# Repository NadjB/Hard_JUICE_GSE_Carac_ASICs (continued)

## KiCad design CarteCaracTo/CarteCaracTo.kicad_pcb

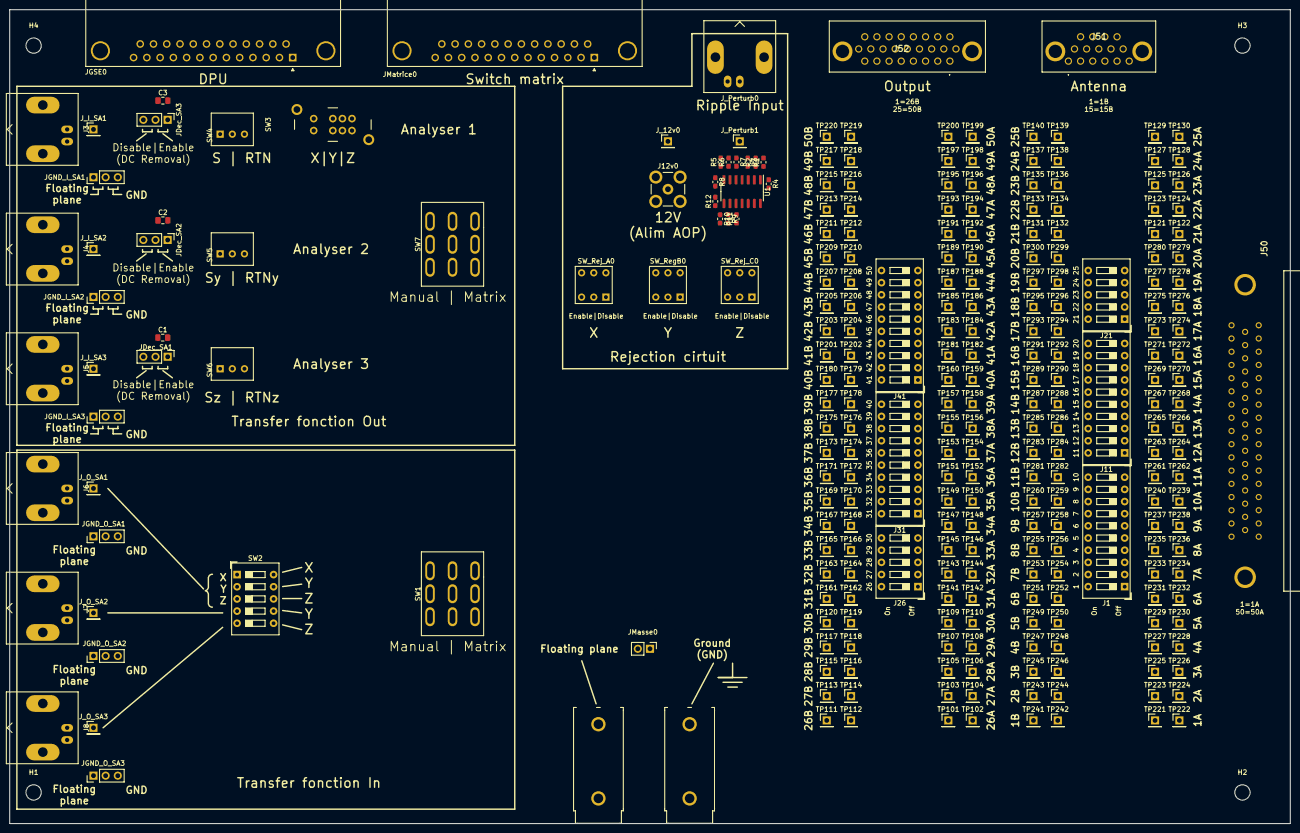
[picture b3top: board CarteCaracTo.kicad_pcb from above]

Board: 6 copper layers, 267.5 x 170.0 mm, 269 parts (0 on the bottom side), 129 nets, no tracks yet.

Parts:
C1, C2, C3: C; C_0805_2012Metric_Pad1.15x1.40mm_HandSolder
H1, H2, H3, H4: MountingHole; MountingHole_3.2mm_M3
J1, J11, J31, J41: Conn_02x10_Counter_Clockwise; SW_DIP_SPSTx10_Slide_9.78x27.58mm_W7.62mm_P2.54mm
J3, J4, J5, J6, J7, J8: Conn_Coaxial; BNC_Amphenol_B6252HB-NPP3G-50_Horizontal
J12v0: Conn_Coaxial; SMB_Jack_Vertical
J21, J26: Conn_02x05_Counter_Clockwise; SW_DIP_SPSTx05_Slide_9.78x14.88mm_W7.62mm_P2.54mm
J50: Sub-D50_F; DD50S564TLF
J51: DB15_Male_MountingHoles; DCCM15PCBRPN
J52: DB25_Female_MountingHoles; DCCM25SCBRPN
JDec_SA1, JDec_SA2, JDec_SA3: Conn_01x03; PinHeader_1x03_P2.54mm_Vertical
JGND_I_SA1, JGND_I_SA2, JGND_I_SA3: Conn_01x03; PinHeader_1x03_P2.54mm_Vertical
JGND_O_SA1, JGND_O_SA2, JGND_O_SA3: Conn_01x03; PinHeader_1x03_P2.54mm_Vertical
JGSE0: DB25_Male_MountingHoles; DSUB-25_Male_Horizontal_P2.77x2.84mm_EdgePinOffset9.90mm_Ho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
JMasse0: Conn_01x02; PinHeader_1x02_P2.54mm_Vertical
JMatrice0: DB25_Male_MountingHoles; DSUB-25_Male_Horizontal_P2.77x2.84mm_EdgePinOffset9.90mm_Ho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
J_12v0: Conn_01x01; PinHeader_1x01_P2.54mm_Vertical
J_I_SA1, J_I_SA2, J_I_SA3: Conn_01x01; PinHeader_1x01_P2.54mm_Vertical
J_O_SA1, J_O_SA2, J_O_SA3: Conn_01x01; PinHeader_1x01_P2.54mm_Vertical
J_Perturb0: Conn_Coaxial; BNC_Amphenol_B6252HB-NPP3G-50_Horizontal
J_Perturb1: Conn_01x01; PinHeader_1x01_P2.54mm_Vertical
R1, R2, R3, R4, R5, R6, R7, R8, R9, R10, R11, R12: R; R_0603_1608Metric_Pad1.05x0.95mm_HandSolder
SW1, SW7: SW_3PDT; SW_3PDT_M2032TNW01_NKK
SW2: SW_DIP_x05; SW_DIP_SPSTx05_Slide_9.78x14.88mm_W7.62mm_P2.54mm
SW3: SW_Slide_DP3T; Switch_DP3T_Slide_MHS233K
SW4, SW5, SW6: SW_SPDT; SW_SPDT_B12AP_NKK
SW_RegB0: SW_Push_DPDT; SW_DPDT_B22AP_NKK
SW_Rej_A0: SW_Push_DPDT; SW_DPDT_B22AP_NKK
SW_Rej_C0: SW_Push_DPDT; SW_DPDT_B22AP_NKK
TP101, TP102, TP103, TP104, TP105, TP106, TP107, TP108, TP109, TP110, TP111, TP112, TP113, TP114, TP115, TP116, TP117, TP118, TP119, TP120, TP121, TP122, TP123, TP124, TP125, TP126, TP127, TP128, TP129, TP130, TP131, TP132, TP133, TP134, TP135, TP136, TP137, TP138, TP139, TP140, TP141, TP142, TP143, TP144, TP145, TP146, TP147, TP148, TP149, TP150, TP151, TP152, TP153, TP154, TP155, TP156, TP157, TP158, TP159, TP160, TP161, TP162, TP163, TP164, TP165, TP166, TP167, TP168, TP169, TP170, TP171, TP172, TP173, TP174, TP175, TP176, TP177, TP178, TP179, TP180, TP181, TP182, TP183, TP184, TP185, TP186, TP187, TP188, TP189, TP190, TP191, TP192, TP193, TP194, TP195, TP196, TP197, TP198, TP199, TP200, TP201, TP202, TP203, TP204, TP205, TP206, TP207, TP208, TP209, TP210, TP211, TP212, TP213, TP214, TP215, TP216, TP217, TP218, TP219, TP220, TP221, TP222, TP223, TP224, TP225, TP226, TP227, TP228, TP229, TP230, TP231, TP232, TP233, TP234, TP235, TP236, TP237, TP238, TP239, TP240, TP241, TP242, TP243, TP244, TP245, TP246, TP247, TP248, TP249, TP250, TP251, TP252, TP253, TP254, TP255, TP256, TP257, TP258, TP259, TP260, TP261, TP262, TP263, TP264, TP265, TP266, TP267, TP268, TP269, TP270, TP271, TP272, TP273, TP274, TP275, TP276, TP277, TP278, TP279, TP280, TP281, TP282, TP283, TP284, TP285, TP286, TP287, TP288, TP289, TP290, TP291, TP292, TP293, TP294, TP295, TP296, TP297, TP298, TP299, TP300: TestPoint; PinHeader_1x01_P2.54mm_Vertical
TPGND0: TestPoint; Banana_test_point_4mm
TPV0: TestPoint; Banana_test_point_4mm
U1: OPA4376; SOIC-14_3.9x8.7mm_P1.27mm

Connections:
/1: J1.1, J50.1, JMatrice0.1, SW2.10, TP221.1, TP222.1
/01-10/1b-10b/sheet61AD0B7F/TPs: TP257.1, TP258.1
/01-10/sheet61ADBB5A/sheet61AD0B7F/TPs: TP237.1, TP238.1
/2: J1.2, J50.2, TP223.1, TP224.1
/3: J1.3, J50.3, JMatrice0.3, SW2.7, SW2.9, TP225.1, TP226.1
/4: J1.4, J50.4, TP227.1, TP228.1
/5: J1.5, J50.5, JMatrice0.5, SW2.6, SW2.8, TP229.1, TP230.1
/6: J1.6, J50.6, TP231.1, TP232.1
/9: J1.9, J50.9, JGSE0.3
/11: J11.1, J50.11, JGSE0.6, TP261.1, TP262.1
/11-20/1b-10b/sheet61AD0B7F/TPs: TP297.1, TP298.1
/11-20/sheet61ADBB5A/sheet61AD0B7F/TPs: TP277.1, TP278.1
/13: J11.3, J50.13, JGSE0.9, TP265.1, TP266.1
/16: J11.6, J50.16, TP271.1, TP272.1
/17: J11.7, J50.17, TP273.1, TP274.1
/18: J11.8, J50.18, TP275.1, TP276.1
/19: J11.9, J50.19, JGSE0.10
/20: J11.10, J50.20, JGSE0.11, TP279.1, TP280.1
/21: J21.1, J50.21, JGSE0.12, TP121.1, TP122.1
/22: J21.2, J50.22, JGSE0.14, TP123.1, TP124.1
/23: J21.3, J50.23, JGSE0.15, TP125.1, TP126.1
/24: J21.4, J50.24, JGSE0.16, TP127.1, TP128.1
/25: J21.5, J50.25, TP129.1, TP130.1
/26: J26.1, J50.26, JGSE0.2, JMatrice0.8, SW3.5, TP101.1, TP102.1
/27: J26.2, J50.27, JGSE0.1, JMatrice0.2, SW3.1, TP103.1, TP104.1
/29: J26.4, J50.29, JGSE0.7, JMatrice0.6, SW3.4, SW6.1, TP107.1, TP108.1
/30: J26.5, J50.30, JGSE0.8, JMatrice0.12, SW3.8, SW6.3, TP109.1, TP110.1
/31: J1.8, J31.1, J50.8, J50.31, TP141.1, TP142.1, TP235.1, TP236.1
/31-40/1b-10b/sheet61AD0B7F/TPs: TP177.1, TP178.1
/31-40/sheet61ADBB5A/sheet61AD0B7F/TPs: TP157.1, TP158.1
/32: J31.2, J50.32, TP143.1, TP144.1
/37: J31.7, J50.37, TP153.1, TP154.1
/40: J31.10, J50.40, JGSE0.4, JMatrice0.4, SW3.3, SW5.1, TP159.1, TP160.1
/41: J41.1, J50.41, JGSE0.5, JMatrice0.10, SW3.7, SW5.3, TP181.1, TP182.1
/41-50/1b-10b/sheet61AD0B7F/TPs: TP217.1, TP218.1
/41-50/sheet61ADBB5A/sheet61AD0B7F/TPs: TP197.1, TP198.1
/43: J1.7, J41.3, J50.7, J50.43, TP185.1, TP186.1, TP233.1, TP234.1
/44: J41.4, J50.44, TP187.1, TP188.1
/101: J1.20, J51.1, TP241.1, TP242.1
/102: J1.19, J51.2, TP243.1, TP244.1
/103: J1.18, J51.3, TP245.1, TP246.1
/104: J1.17, J51.4, TP247.1, TP248.1
/105: J1.16, J51.5, TP249.1, TP250.1
/106: J1.15, J51.6, TP251.1, TP252.1
/107: J1.14, J51.7, TP253.1, TP254.1
/108: J1.13, J51.8, TP255.1, TP256.1
/109: J1.12, J51.9
/111: J11.20, J51.11, TP281.1, TP282.1
/113: J11.18, J51.13, TP285.1, TP286.1
/116: J11.15, TP291.1, TP292.1
/117: J11.14, TP293.1, TP294.1
/118: J11.13, TP295.1, TP296.1
/120: J11.11, TP299.1, TP300.1
/121: J21.10, TP131.1, TP132.1
/122: J21.9, TP133.1, TP134.1
/123: J21.8, TP135.1, TP136.1
/124: J21.7, TP137.1, TP138.1
/125: J21.6, TP139.1, TP140.1
/126: J26.10, J52.1, TP111.1, TP112.1
/127: J26.9, J52.2, TP113.1, TP114.1
/129: J26.7, J52.4, TP117.1, TP118.1
/130: J26.6, J52.5, TP119.1, TP120.1
/131: J31.20, J52.6, TP161.1, TP162.1
/132: J31.19, J52.7, TP163.1, TP164.1
/134: J31.17, J52.9, TP167.1, TP168.1
/137: J31.14, J52.12, TP173.1, TP174.1
/140: J31.11, J52.15, TP179.1, TP180.1
/141: J41.20, J52.16, TP201.1, TP202.1
/143: J41.18, J52.18, TP205.1, TP206.1
/144: J41.17, J52.19, TP207.1, TP208.1
/145: J41.16, J52.20, TP209.1, TP210.1
/148: J41.13, J52.23, TP215.1, TP216.1
/+6V_A: J41.5, J50.45, SW_Rej_A0.2, TP189.1, TP190.1
/+6V_B: J31.4, J50.34, SW_RegB0.2, TP147.1, TP148.1
/+6V_C: J41.8, J50.48, SW_Rej_C0.2, TP195.1, TP196.1
/+12v: J12v0.1, J_12v0.1, U1.4
/MatriceToSpectro1: JMatrice0.18, SW7.3
/MatriceToSpectro2: JMatrice0.20, SW7.6
/MatriceToSpectro3: JMatrice0.22, SW7.9
/Source+6V_A: JGSE0.17, SW_Rej_A0.5
/Source+6V_B: JGSE0.18, SW_RegB0.5
/Source+6V_C: JGSE0.19, SW_Rej_C0.5
/Spectro1ToMatrice: JMatrice0.17, SW1.3
/Spectro1_In: JDec_SA3.2, SW7.2
/Spectro1_Out: J6.1, J_O_SA1.1, SW1.2
/Spectro1_RTN: SW3.6, SW4.3
/Spectro1_S: SW3.2, SW4.1
/Spectro2ToMatrice: JMatrice0.19, SW1.6
/Spectro2_In: JDec_SA2.2, SW7.5
/Spectro2_Out: J7.1, J_O_SA2.1, SW1.5
/Spectro3ToMatrice: JMatrice0.21, SW1.9
/Spectro3_In: JDec_SA1.2, SW7.8
/Spectro3_Out: J8.1, J_O_SA3.1, SW1.8
/VPerturb: J_Perturb0.1, J_Perturb1.1, R2.2, R6.2, R10.2
GND: J1.10, J1.11, J11.2, J11.4, J11.5, J11.16, J11.17, J11.19, J12v0.2, J26.3, J26.8, J31.3, J31.5, J31.6, J31.8, J31.9, J31.12, J31.13, J31.15, J31.16, J31.18, J41.2, J41.6, J41.7, J41.9, J41.10, J41.11, J41.12, J41.14, J41.15, J41.19, J50.0, J50.10, J50.12, J50.14, J50.15, J50.28, J50.33, J50.35, J50.36, J50.38, J50.39, J50.42, J50.46, J50.47, J50.49, J50.50, J51.0, J51.10, J51.12, J51.14, J51.15, J52.0, J52.3, J52.8, J52.10, J52.11, J52.13, J52.14, J52.17, J52.21, J52.22, J52.24, J52.25, JGND_I_SA1.3, JGND_I_SA2.3, JGND_I_SA3.3, JGND_O_SA1.3, JGND_O_SA2.3, JGND_O_SA3.3, JGSE0.0, JGSE0.13, JGSE0.20, JGSE0.21, JGSE0.22, JGSE0.23, JGSE0.24, JGSE0.25, JMasse0.1, JMatrice0.0, J_Perturb0.2, R3.1, R7.1, R11.1, SW3.0, TP105.1, TP106.1, TP115.1, TP116.1, TP145.1, TP146.1, TP149.1, TP150.1, TP151.1, TP152.1, TP155.1, TP156.1, TP165.1, TP166.1, TP169.1, TP170.1, TP171.1, TP172.1, TP175.1, TP176.1, TP183.1, TP184.1, TP191.1, TP192.1, TP193.1, TP194.1, TP199.1, TP200.1, TP203.1, TP204.1, TP211.1, TP212.1, TP213.1, TP214.1, TP219.1, TP220.1, TP239.1, TP240.1, TP259.1, TP260.1, TP263.1, TP264.1, TP267.1, TP268.1, TP269.1, TP270.1, TP283.1, TP284.1, TP287.1, TP288.1, TP289.1, TP290.1, TPGND0.1, U1.11, U1.12, U1.13, U1.14
GNDREF: JGND_I_SA1.1, JGND_I_SA2.1, JGND_I_SA3.1, JGND_O_SA1.1, JGND_O_SA2.1, JGND_O_SA3.1, JMasse0.2, TPV0.1
unnamed: C1.1, J5.1, JDec_SA1.3, J_I_SA3.1
unnamed: C1.2, JDec_SA1.1
unnamed: C2.1, J4.1, JDec_SA2.3, J_I_SA2.1
unnamed: C2.2, JDec_SA2.1
unnamed: C3.1, J3.1, JDec_SA3.3, J_I_SA1.1
unnamed: C3.2, JDec_SA3.1
unnamed: J3.2, JGND_I_SA1.2
unnamed: J4.2, JGND_I_SA2.2
unnamed: J5.2, JGND_I_SA3.2
unnamed: J6.2, JGND_O_SA1.2
unnamed: J7.2, JGND_O_SA2.2
unnamed: J8.2, JGND_O_SA3.2
unnamed: R1.1, R2.1, U1.2
unnamed: R1.2, SW_Rej_A0.6
unnamed: R3.2, R4.2, U1.3
unnamed: R4.1, SW_Rej_A0.3, U1.1
unnamed: R5.1, R6.1, U1.6
unnamed: R5.2, SW_RegB0.6
unnamed: R7.2, R8.2, U1.5
unnamed: R8.1, SW_RegB0.3, U1.7
unnamed: R9.2, SW_Rej_C0.6
unnamed: R9.1, R10.1, U1.9
unnamed: R11.2, R12.2, U1.10
unnamed: R12.1, SW_Rej_C0.3, U1.8
unnamed: SW1.1, SW2.1, SW2.2, SW2.3
unnamed: SW1.4, SW2.4
unnamed: SW1.7, SW2.5
unnamed: SW4.2, SW7.1
unnamed: SW5.2, SW7.4
unnamed: SW6.2, SW7.7
unnamed: SW_RegB0.1, SW_RegB0.4
unnamed: SW_Rej_A0.1, SW_Rej_A0.4
unnamed: SW_Rej_C0.1, SW_Rej_C0.4

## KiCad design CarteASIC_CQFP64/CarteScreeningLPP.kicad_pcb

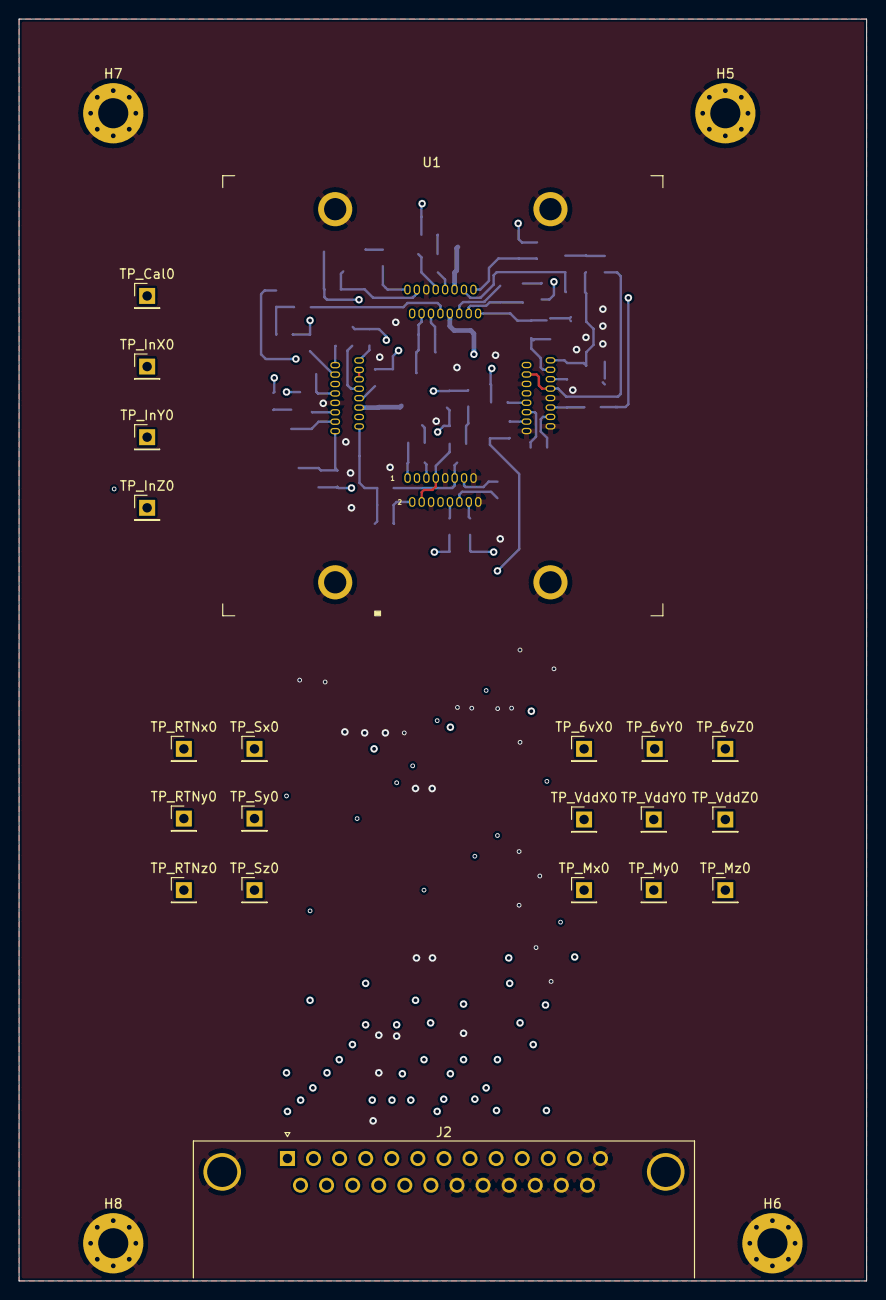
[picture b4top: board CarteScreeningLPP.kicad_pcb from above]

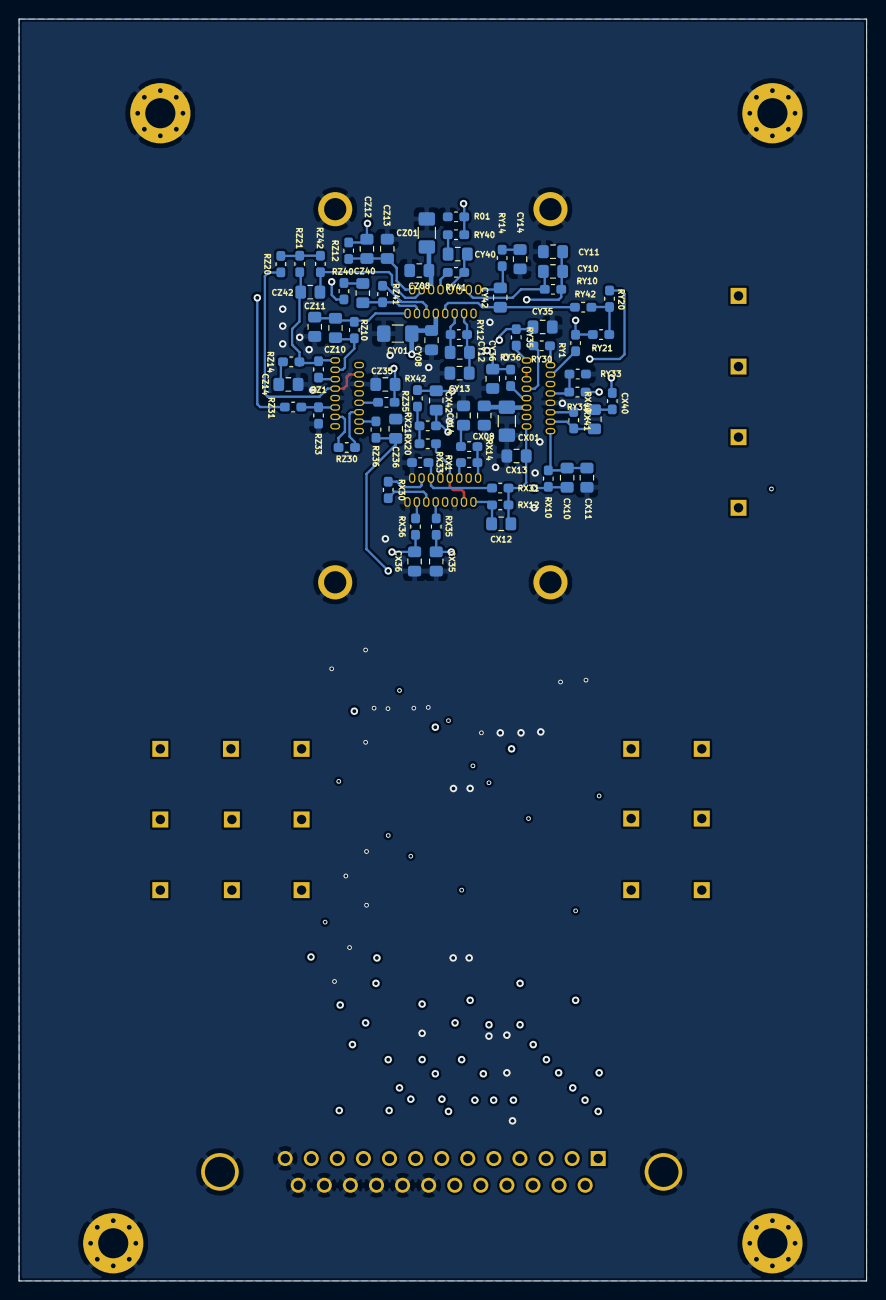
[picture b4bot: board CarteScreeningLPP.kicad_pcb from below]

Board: 4 copper layers, 90.0 x 134.0 mm, 101 parts (76 on the bottom side), 65 nets.

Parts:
CX01: 2,7µ; C_1206_3216Metric_Pad1.42x1.75mm_HandSolder
CX08, CX35, CX36: 1n; C_0805_2012Metric_Pad1.15x1.40mm_HandSolder
CX10, CX12: 150p; C_0805_2012Metric_Pad1.15x1.40mm_HandSolder
CX11, CX40: 220n; C_0805_2012Metric_Pad1.15x1.40mm_HandSolder
CX13: 390n; C_0805_2012Metric_Pad1.15x1.40mm_HandSolder
CX14: 560n; C_0805_2012Metric_Pad1.15x1.40mm_HandSolder
CX42: 2,21n(2,2n); C_0805_2012Metric_Pad1.15x1.40mm_HandSolder
CY01: 2,7µ; C_1206_3216Metric_Pad1.42x1.75mm_HandSolder
CY08, CY35, CY36: 1n; C_0805_2012Metric_Pad1.15x1.40mm_HandSolder
CY10, CY12: 150p; C_0805_2012Metric_Pad1.15x1.40mm_HandSolder
CY11, CY40: 220n; C_0805_2012Metric_Pad1.15x1.40mm_HandSolder
CY13: 390n; C_0805_2012Metric_Pad1.15x1.40mm_HandSolder
CY14: 560n; C_0805_2012Metric_Pad1.15x1.40mm_HandSolder
CY42: 2,21n(2,2n); C_0805_2012Metric_Pad1.15x1.40mm_HandSolder
CZ01: 2,7µ; C_1206_3216Metric_Pad1.42x1.75mm_HandSolder
CZ08, CZ35, CZ36: 1n; C_0805_2012Metric_Pad1.15x1.40mm_HandSolder
CZ10, CZ12: 150p; C_0805_2012Metric_Pad1.15x1.40mm_HandSolder
CZ11, CZ40: 220n; C_0805_2012Metric_Pad1.15x1.40mm_HandSolder
CZ13: 390n; C_0805_2012Metric_Pad1.15x1.40mm_HandSolder
CZ14: 560n; C_0805_2012Metric_Pad1.15x1.40mm_HandSolder
CZ42: 2,21n(2,2n); C_0805_2012Metric_Pad1.15x1.40mm_HandSolder
H5, H6, H7, H8: MountingHole_Pad; MountingHole_3.2mm_M3_Pad_Via
J2: DB25_Male_MountingHoles; DSUB-25_Male_Horizontal_P2.77x2.84mm_EdgePinOffset9.90mm_Ho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
R01: 10k; R_0603_1608Metric_Pad1.05x0.95mm_HandSolder
RX1: 499; R_0603_1608Metric_Pad1.05x0.95mm_HandSolder
RX10: 26,7k; R_0603_1608Metric_Pad1.05x0.95mm_HandSolder
RX12, RX31, RX33, RX41: 49,9k; R_0603_1608Metric_Pad1.05x0.95mm_HandSolder
RX14: 100; R_0603_1608Metric_Pad1.05x0.95mm_HandSolder
RX20: 68k; R_0603_1608Metric_Pad1.05x0.95mm_HandSolder
RX21: 5; R_0603_1608Metric_Pad1.05x0.95mm_HandSolder
RX30, RX35, RX36: 7,5k; R_0603_1608Metric_Pad1.05x0.95mm_HandSolder
RX40: 750k; R_0603_1608Metric_Pad1.05x0.95mm_HandSolder
RX42: 42,2k; R_0603_1608Metric_Pad1.05x0.95mm_HandSolder
RY1: 499; R_0603_1608Metric_Pad1.05x0.95mm_HandSolder
RY10: 26,7k; R_0603_1608Metric_Pad1.05x0.95mm_HandSolder
RY12, RY31, RY33, RY41: 49,9k; R_0603_1608Metric_Pad1.05x0.95mm_HandSolder
RY14: 100; R_0603_1608Metric_Pad1.05x0.95mm_HandSolder
RY20: 68k; R_0603_1608Metric_Pad1.05x0.95mm_HandSolder
RY21: 5; R_0603_1608Metric_Pad1.05x0.95mm_HandSolder
RY30, RY35, RY36: 7,5k; R_0603_1608Metric_Pad1.05x0.95mm_HandSolder
RY40: 750k; R_0603_1608Metric_Pad1.05x0.95mm_HandSolder
RY42: 42,2k; R_0603_1608Metric_Pad1.05x0.95mm_HandSolder
RZ1: 499; R_0603_1608Metric_Pad1.05x0.95mm_HandSolder
RZ10: 26,7k; R_0603_1608Metric_Pad1.05x0.95mm_HandSolder
RZ12, RZ31, RZ33, RZ41: 49,9k; R_0603_1608Metric_Pad1.05x0.95mm_HandSolder
RZ14: 100; R_0603_1608Metric_Pad1.05x0.95mm_HandSolder
RZ20: 68k; R_0603_1608Metric_Pad1.05x0.95mm_HandSolder
RZ21: 5; R_0603_1608Metric_Pad1.05x0.95mm_HandSolder
RZ30, RZ35, RZ36: 7,5k; R_0603_1608Metric_Pad1.05x0.95mm_HandSolder
RZ40: 750k; R_0603_1608Metric_Pad1.05x0.95mm_HandSolder
RZ42: 42,2k; R_0603_1608Metric_Pad1.05x0.95mm_HandSolder
TP_6vX0, TP_6vY0, TP_6vZ0: TestPoint; PinHeader_1x01_P2.54mm_Vertical
TP_Cal0: TestPoint; PinHeader_1x01_P2.54mm_Vertical
TP_InX0: TestPoint; PinHeader_1x01_P2.54mm_Vertical
TP_InY0: TestPoint; PinHeader_1x01_P2.54mm_Vertical
TP_InZ0: TestPoint; PinHeader_1x01_P2.54mm_Vertical
TP_Mx0: TestPoint; PinHeader_1x01_P2.54mm_Vertical
TP_My0: TestPoint; PinHeader_1x01_P2.54mm_Vertical
TP_Mz0: TestPoint; PinHeader_1x01_P2.54mm_Vertical
TP_RTNx0: TestPoint; PinHeader_1x01_P2.54mm_Vertical
TP_RTNy0: TestPoint; PinHeader_1x01_P2.54mm_Vertical
TP_RTNz0: TestPoint; PinHeader_1x01_P2.54mm_Vertical
TP_Sx0: TestPoint; PinHeader_1x01_P2.54mm_Vertical
TP_Sy0: TestPoint; PinHeader_1x01_P2.54mm_Vertical
TP_Sz0: TestPoint; PinHeader_1x01_P2.54mm_Vertical
TP_VddX0: TestPoint; PinHeader_1x01_P2.54mm_Vertical
TP_VddY0: TestPoint; PinHeader_1x01_P2.54mm_Vertical
TP_VddZ0: TestPoint; PinHeader_1x01_P2.54mm_Vertical
U1: ASIC_JUICE; 8500-50mm-64T-Ovale-EuroCircuitOK

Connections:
/+6V_X: CX01.1, CX08.1, J2.17, TP_6vX0.1, U1.59
/+6V_Y: CY01.1, CY08.1, J2.18, TP_6vY0.1, U1.39
/+6V_Z: CZ01.1, CZ08.1, J2.19, TP_6vZ0.1, U1.38
/AsicScreening01/CAL_Gain_X: RX41.1, U1.60
/AsicScreening01/CAL_Gain_Y: RY41.1, U1.40
/AsicScreening01/CAL_Gain_Z: RZ41.1, U1.37
/AsicScreening01/CAL_In_X: CX40.1, RX41.2, U1.62
/AsicScreening01/CAL_In_Y: CY40.1, RY41.2, U1.42
/AsicScreening01/CAL_In_Z: CZ40.1, RZ41.2, U1.35
/AsicScreening01/CAL_Out_X: CX42.1, RX42.1, U1.61
/AsicScreening01/CAL_Out_Y: CY42.1, RY42.1, U1.41
/AsicScreening01/CAL_Out_Z: CZ42.1, RZ42.1, U1.36
/AsicScreening01/CR_X: RX20.2, RX21.1, RX42.2
/AsicScreening01/CR_Y: RY20.2, RY21.1, RY42.2
/AsicScreening01/CR_Z: RZ20.2, RZ21.1, RZ42.2
/AsicScreening01/Gain_Out2_N_X: RX30.2, U1.12
/AsicScreening01/Gain_Out2_N_Y: RY30.2, U1.55
/AsicScreening01/Gain_Out2_N_Z: RZ30.2, U1.21
/AsicScreening01/Gain_Out2_P_X: RX30.1, U1.13
/AsicScreening01/Gain_Out2_P_Y: RY30.1, U1.50
/AsicScreening01/Gain_Out2_P_Z: RZ30.1, U1.20
/AsicScreening01/In2N_X: RX31.1, RX33.1, U1.11
/AsicScreening01/In2N_Y: RY31.1, RY33.1, U1.56
/AsicScreening01/In2N_Z: RZ31.1, RZ33.1, U1.22
/AsicScreening01/In2P_X: RX20.1, U1.4, U1.7
/AsicScreening01/In2P_Y: RY20.1, U1.51, U1.53
/AsicScreening01/In2P_Z: RZ20.1, U1.26, U1.29
/AsicScreening01/Out2_NInv_X: RX35.2, U1.10
/AsicScreening01/Out2_NInv_Y: RY35.2, U1.49
/AsicScreening01/Out2_NInv_Z: RZ35.2, U1.23
/AsicScreening01/Out2_inv_X: RX36.2, U1.14
/AsicScreening01/Out2_inv_Y: RY36.2, U1.57
/AsicScreening01/Out2_inv_Z: RZ36.2, U1.19
/AsicScreening01/Regu_Bias_LNA_X: CX10.2, RX10.2, U1.3
/AsicScreening01/Regu_Bias_LNA_Y: CY10.2, RY10.2, U1.46
/AsicScreening01/Regu_Bias_LNA_Z: CZ10.2, RZ10.2, U1.30
/AsicScreening01/Regu_VDD_X: CX12.2, RX12.2, U1.2
/AsicScreening01/Regu_VDD_Y: CY12.2, RY12.2, U1.43
/AsicScreening01/Regu_VDD_Z: CZ12.2, RZ12.2, U1.31
/CAL: R01.1, RX40.2, RY40.2, RZ40.2, TP_Cal0.1
/In1P_X: RX1.1, TP_InX0.1, U1.5
/In1P_Y: RY1.1, TP_InY0.1, U1.52
/In1P_Z: RZ1.1, TP_InZ0.1, U1.28
/M_X: CX42.2, J2.3, RX1.2, RX14.1, RX21.2, TP_Mx0.1, U1.1
/M_Y: CY42.2, J2.6, RY1.2, RY14.1, RY21.2, TP_My0.1, U1.48
/M_Z: CZ42.2, J2.9, RZ1.2, RZ14.1, RZ21.2, TP_Mz0.1, U1.32
/RTNx: CX36.1, J2.2, RX36.1, TP_RTNx0.1
/RTNy: CY36.1, J2.5, RY36.1, TP_RTNy0.1
/RTNz: CZ36.1, J2.8, RZ36.1, TP_RTNz0.1
/Sx: CX35.1, J2.1, RX35.1, TP_Sx0.1
/Sy: CY35.1, J2.4, RY35.1, TP_Sy0.1
/Sz: CZ35.1, J2.7, RZ35.1, TP_Sz0.1
/VDD_X: CX12.1, CX13.1, J2.14, RX12.1, RX31.2, TP_VddX0.1, U1.63
/VDD_Y: CY12.1, CY13.1, J2.15, RY12.1, RY31.2, TP_VddY0.1, U1.45
/VDD_Z: CZ12.1, CZ13.1, J2.16, RZ12.1, RZ31.2, TP_VddZ0.1, U1.34
/V_BIAS_LNA_X: CX10.1, CX11.1, J2.10, RX10.1, U1.64
/V_BIAS_LNA_Y: CY10.1, CY11.1, J2.11, RY10.1, U1.47
/V_BIAS_LNA_Z: CZ10.1, CZ11.1, J2.12, RZ10.1, U1.33
GND: CX01.2, CX08.2, CX11.2, CX13.2, CX14.2, CX35.2, CX36.2, CY01.2, CY08.2, CY11.2, CY13.2, CY14.2, CY35.2, CY36.2, CZ01.2, CZ08.2, CZ11.2, CZ13.2, CZ14.2, CZ35.2, CZ36.2, H5.1, H6.1, H7.1, H8.1, J2.0, J2.13, J2.20, J2.21, J2.22, J2.23, J2.24, J2.25, R01.2, RX33.2, RY33.2, RZ33.2, U1.6, U1.9, U1.15, U1.16, U1.17, U1.18, U1.24, U1.27, U1.44, U1.58, U1.65, U1.66, U1.67, U1.68
unnamed: CX14.1, RX14.2
unnamed: CX40.2, RX40.1
unnamed: CY14.1, RY14.2
unnamed: CY40.2, RY40.1
unnamed: CZ14.1, RZ14.2
unnamed: CZ40.2, RZ40.1

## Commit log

2019-12-20 Signaux ASIC sortis
2019-12-20 20-12-19
2019-12-24 Del des point de tests et redimentionnement
2019-12-27 Added 2nd card
2019-12-27 mineur
2019-12-31 Mise en forme de la carte + version carte ASIC et Carac separées
2020-01-03 ID des pins, option capa sur sortie, option GND ou plan de masse sur BNC
2020-01-03 Ajout de VDD et Vbias sur le 50 pins (reste 2)
2020-01-04 Add files via upload
    Schematique conn 78 pins carte ASIC <==> carte carac
2020-01-08 v0 near finished
2020-01-08 Pre-routage
2020-01-08 cleaning Pre-routage
2020-01-10 Routé, verif pre-envoie
2020-01-14 Envoyé en prod
2020-03-23 Correction pinout 6P3T & ajout d'étiquettes sur pin hiérarchique 3P4T + routage
2020-03-23 Mise en conformité valeurs PFM
2020-03-24 Correction et amélioration de la sérigraphie
2021-12-06 Deleted unused Added local componants
